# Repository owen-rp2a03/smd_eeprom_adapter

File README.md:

# SMD to THT Under-side EEPROM Adapter

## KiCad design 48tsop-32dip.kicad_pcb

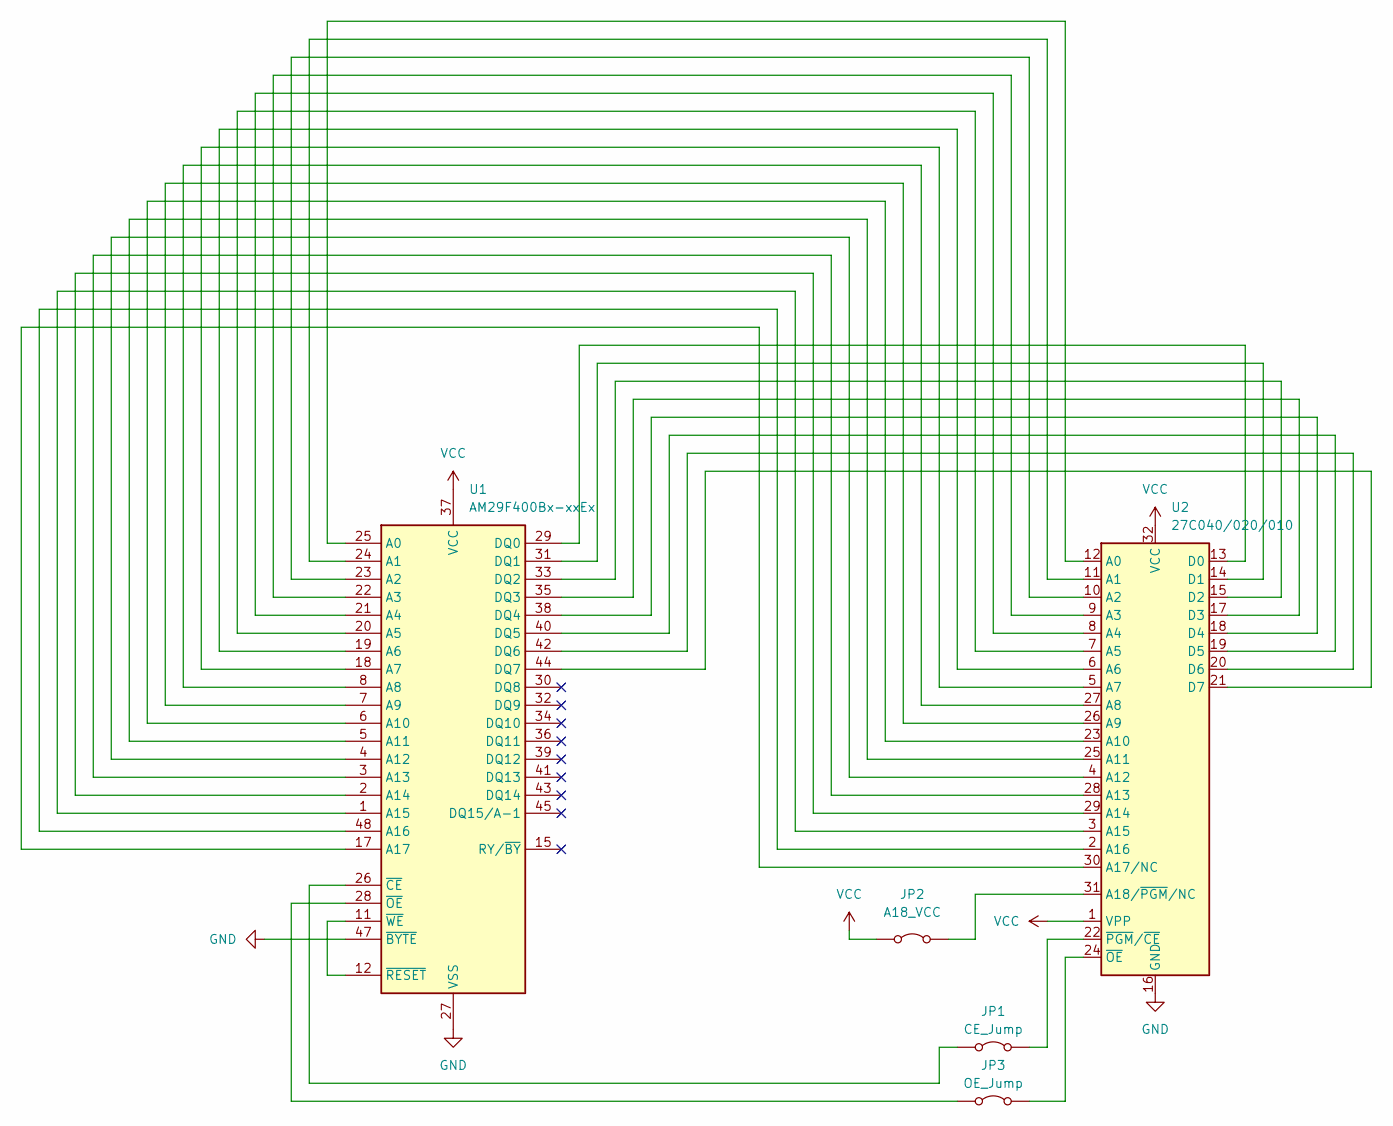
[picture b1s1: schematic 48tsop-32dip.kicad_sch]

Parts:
JP1: CE_Jump; SolderJumper-2_P1.3mm_Bridged_Pad1.0x1.5mm
JP2: A18_VCC; SolderJumper-2_P1.3mm_Bridged_Pad1.0x1.5mm
JP3: OE_Jump; SolderJumper-2_P1.3mm_Bridged_Pad1.0x1.5mm
U1: AM29F400Bx-xxEx; TSOP-I-48_18.4x12mm_P0.5mm
U2: 27C040/020/010

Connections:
GND: U1.27 (VSS), U1.46 (VSS), U1.47 (~BYTE), U2.16 (GND)
unnamed: JP1.1 (A), U1.26 (~CE)
unnamed: JP1.2 (B), U2.22 (~PGM/~CE)
unnamed: JP2.1 (A), U2.31 (A18/~PGM/NC)
unnamed: JP3.1 (A), U1.28 (~OE)
unnamed: JP3.2 (B), U2.24 (~OE)
unnamed: U1.25 (A0), U2.12 (A0)
unnamed: U1.24 (A1), U2.11 (A1)
unnamed: U1.23 (A2), U2.10 (A2)
unnamed: U1.22 (A3), U2.9 (A3)
unnamed: U1.21 (A4), U2.8 (A4)
unnamed: U1.20 (A5), U2.7 (A5)
unnamed: U1.19 (A6), U2.6 (A6)
unnamed: U1.18 (A7), U2.5 (A7)
unnamed: U1.8 (A8), U2.27 (A8)
unnamed: U1.7 (A9), U2.26 (A9)
unnamed: U1.6 (A10), U2.23 (A10)
unnamed: U1.5 (A11), U2.25 (A11)
unnamed: U1.4 (A12), U2.4 (A12)
unnamed: U1.3 (A13), U2.28 (A13)
unnamed: U1.2 (A14), U2.29 (A14)
unnamed: U1.1 (A15), U2.3 (A15)
unnamed: U1.48 (A16), U2.2 (A16)
unnamed: U1.17 (A17), U2.30 (A17/NC)
unnamed: U1.29 (DQ0), U2.13 (D0)
unnamed: U1.31 (DQ1), U2.14 (D1)
unnamed: U1.33 (DQ2), U2.15 (D2)
unnamed: U1.35 (DQ3), U2.17 (D3)
unnamed: U1.38 (DQ4), U2.18 (D4)
unnamed: U1.40 (DQ5), U2.19 (D5)
unnamed: U1.42 (DQ6), U2.20 (D6)
unnamed: U1.44 (DQ7), U2.21 (D7)
unnamed: U1.11 (~WE), U1.12 (~RESET)
VCC: JP2.2 (B), U1.37 (VCC), U2.1 (VPP), U2.32 (VCC)

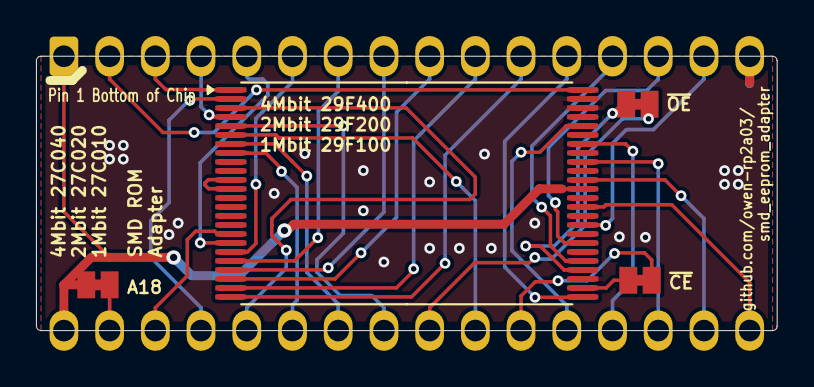
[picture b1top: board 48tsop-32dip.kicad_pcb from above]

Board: 2 copper layers, 41.1 x 15.2 mm, 5 parts (0 on the bottom side), 34 nets.

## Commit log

2026-05-16 gerbers
2026-05-16 imgs
2026-05-16 fix gerber
